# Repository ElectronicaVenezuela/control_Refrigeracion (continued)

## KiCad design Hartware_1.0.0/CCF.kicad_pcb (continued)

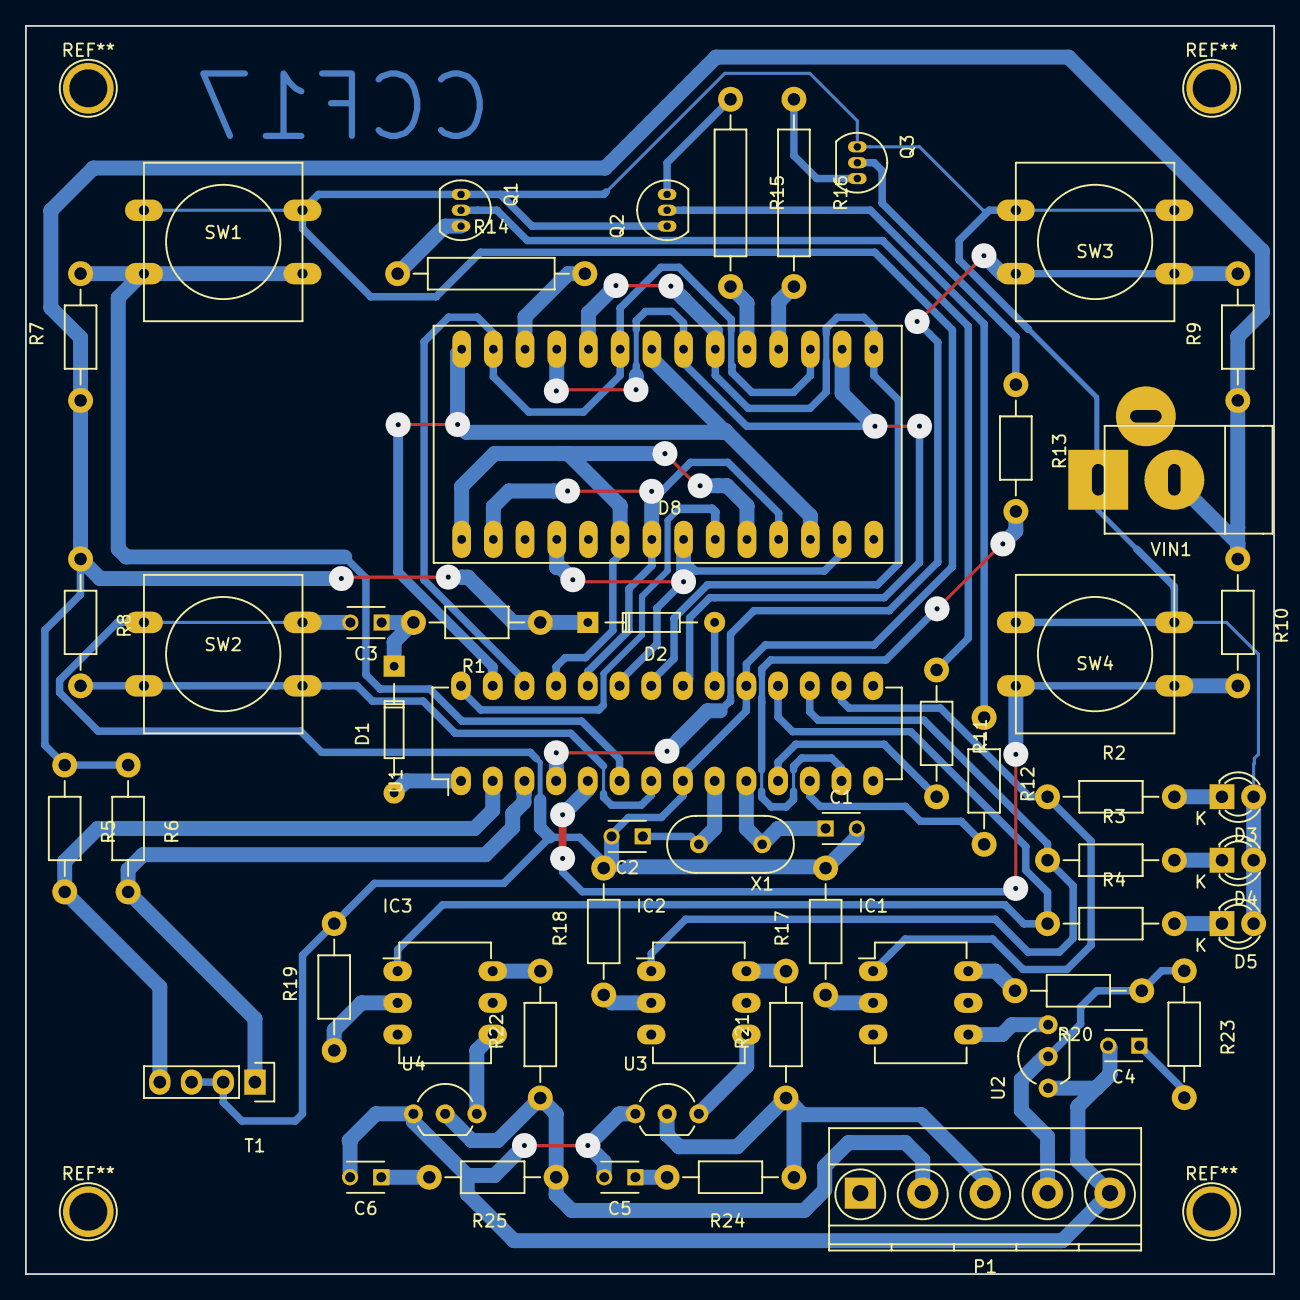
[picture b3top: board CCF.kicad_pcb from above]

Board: 2 copper layers, 100.0 x 100.0 mm, 55 parts (0 on the bottom side), 55 nets.

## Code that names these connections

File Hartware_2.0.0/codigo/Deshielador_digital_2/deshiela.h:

#include <18F2550.h>
#device adc=10

#FUSES NOWDT                    //No Watch Dog Timer
#FUSES WDT128                   //Watch Dog Timer uses 1:128 Postscale
#FUSES PLL1                     //No PLL PreScaler
#FUSES CPUDIV1                  //No System Clock Postscaler
#FUSES NOUSBDIV                 //USB clock source comes from primary oscillator
#FUSES XT                       //Crystal osc <= 4mhz for PCM/PCH , 3mhz to 10 mhz for PCD
#FUSES NOFCMEN                  //Fail-safe clock monitor disabled
#FUSES NOBROWNOUT               //No brownout reset
#FUSES NOLVP                    //No low voltage prgming, B3(PIC16) or B5(PIC18) used for I/O
#FUSES NOXINST                  //Extended set extension and Indexed Addressing mode disabled (Legacy mode)

///SALIDAS
#DEFINE COMPRESOR       PIN_C5
#DEFINE VENTILADOR      PIN_C6
#DEFINE RESISTENCIA     PIN_C7

///USUARIO
#DEFINE BOTON_PROGRA    PIN_A2
#DEFINE BOTON_SELECT    PIN_A3
#DEFINE BOTON_MAS       PIN_A4
#DEFINE BOTON_MENOS     PIN_A5

#use delay(clock=4000000)

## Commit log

2018-02-07 inicio control de tesis
2018-02-08 primer trabajo de codificacion
2018-02-08 modificacion de cartas
2018-02-12 a medio hacer
2018-02-12 modificando Readme
2018-02-12 final placa v2
2018-02-13 termino parcial de la version 2
2018-02-13 agregando BOM
2018-02-13 creando archivo step
2018-02-18 agregando archivos finales
2018-02-18 marcando tesis
2018-02-18 finalinzando la placa
2018-02-19 colocando conector de JST de 90grados
2018-03-02 lista por hacer
2018-03-15 agregando carta de le empresa y modificando tomo
2018-03-15 modificando carta de la empresa
2018-04-14 agregando omega
2018-04-14 agregando modelo 3d
2018-04-14 agregando stp
2018-04-26 culminando hartware omega 2
2018-06-08 pasandome a mac
